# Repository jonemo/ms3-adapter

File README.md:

MS3 to Serial Port Adapter
==========================

What is this?
-------------

This repo contains a PCB design project including schematic, board layout, and component library.
The board is meant to provide an interface between three connectors:

* The DB15 connector (aka "VGA connector") attached to a Microscan MS3 barcode reader
* A DB9 connector plugged into the RS-232 "serial" port of a PC (or a USB-to-Serial converter or some other device with serial port)
* A 5.5mm center positive 5V DC power supply cable

When all three connectors are plugged in, the barcode reader is powered and can be communicated with from the PC.
For how to communicate with the barcode reader, please refer to Microscan's user manual or use [Microscan's ESP software](http://www.microscan.com/esp-easy-setup-program-software).
The Python library [microscan-driver](https://github.com/jonemo/microscan-driver) might be of use.

The files were created using Autodesk's Eagle 7.6.0.

Compatibility
-------------

I offer no guarantees that this PCB design works or
The board is almost certainly compatible with other Microscan barcode reader products, but it has only been tested with the MS3.

Sources
-------

The component library in this repo contains many footprints that are copied or modified from [Sparkfun's Eagle footprint library](https://github.com/sparkfun/SparkFun-Eagle-Libraries/).

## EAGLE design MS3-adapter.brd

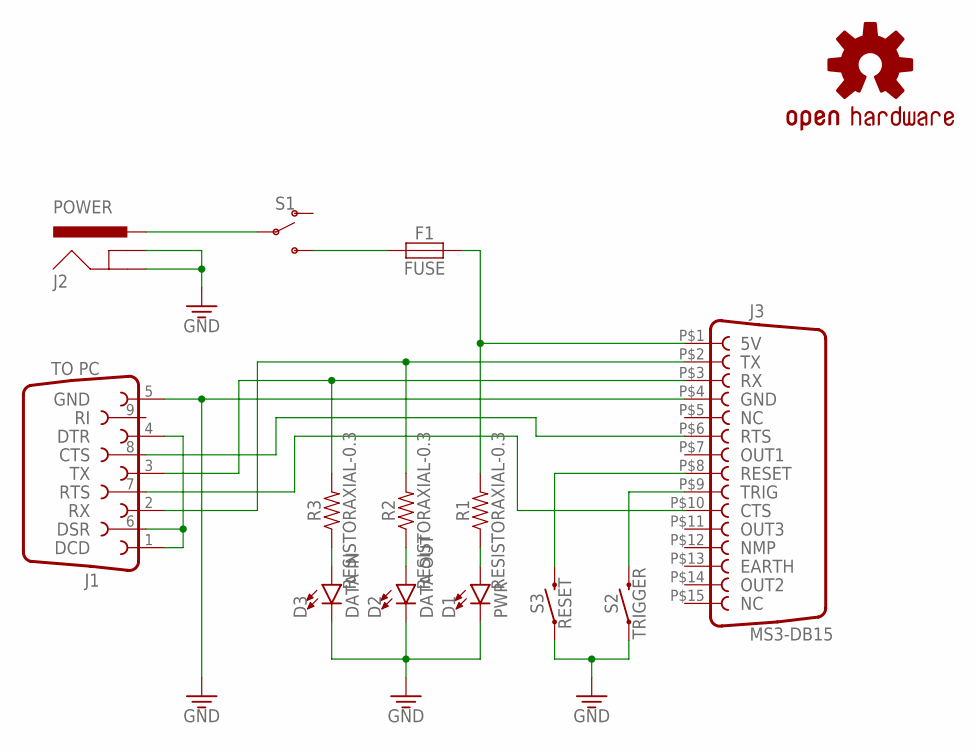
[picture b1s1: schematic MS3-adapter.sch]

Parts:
D1: PWR; LED_5MM
D2: DATA OUT; LED_5MM
D3: DATA IN; LED_5MM
F1: FUSE; FUSEHOLDER-PAIR-5MM
J1: TO PC; DB9-FEMALE
J2: POWER; POWER_JACK_PTH
J3: MS3-DB15; DB15-MALE
LOGO1: OSHW-LOGOS; OSHW-LOGO-S
R1, R2, R3: RESISTORAXIAL-0.3; AXIAL-0.3
S1: SWITCH-SPDT-PTH-11.6X4.0MM; SWITCH_SPDT_PTH_11.6X4.0MM
S2: TRIGGER; TACTILE_SWITCH_PTH_12MM
S3: RESET; TACTILE_SWITCH_PTH_12MM

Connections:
GND: D1.K (C), D2.K (C), D3.K (C), J1.5, J2.GND, J2.GNDBREAK, J3.P$4 (4), S2.1, S3.1
unnamed: J2.PWR, S1.2
unnamed: F1.P$1 (1), F1.P$2 (1), S1.3 (S)
unnamed: J1.3, J3.P$3 (3), R3.P$2 (2)
unnamed: J1.2, J3.P$2 (2), R2.P$2 (2)
unnamed: J1.1, J1.4, J1.6
unnamed: J1.7, J3.P$10 (10)
unnamed: J1.8, J3.P$6 (6)
unnamed: F1.P$3 (2), F1.P$4 (2), J3.P$1 (1), R1.P$2 (2)
unnamed: D2.A, R2.P$1 (1)
unnamed: D1.A, R1.P$1 (1)
unnamed: D3.A, R3.P$1 (1)
unnamed: J3.P$8 (8), S3.3 (2)
unnamed: J3.P$9 (9), S2.3 (2)

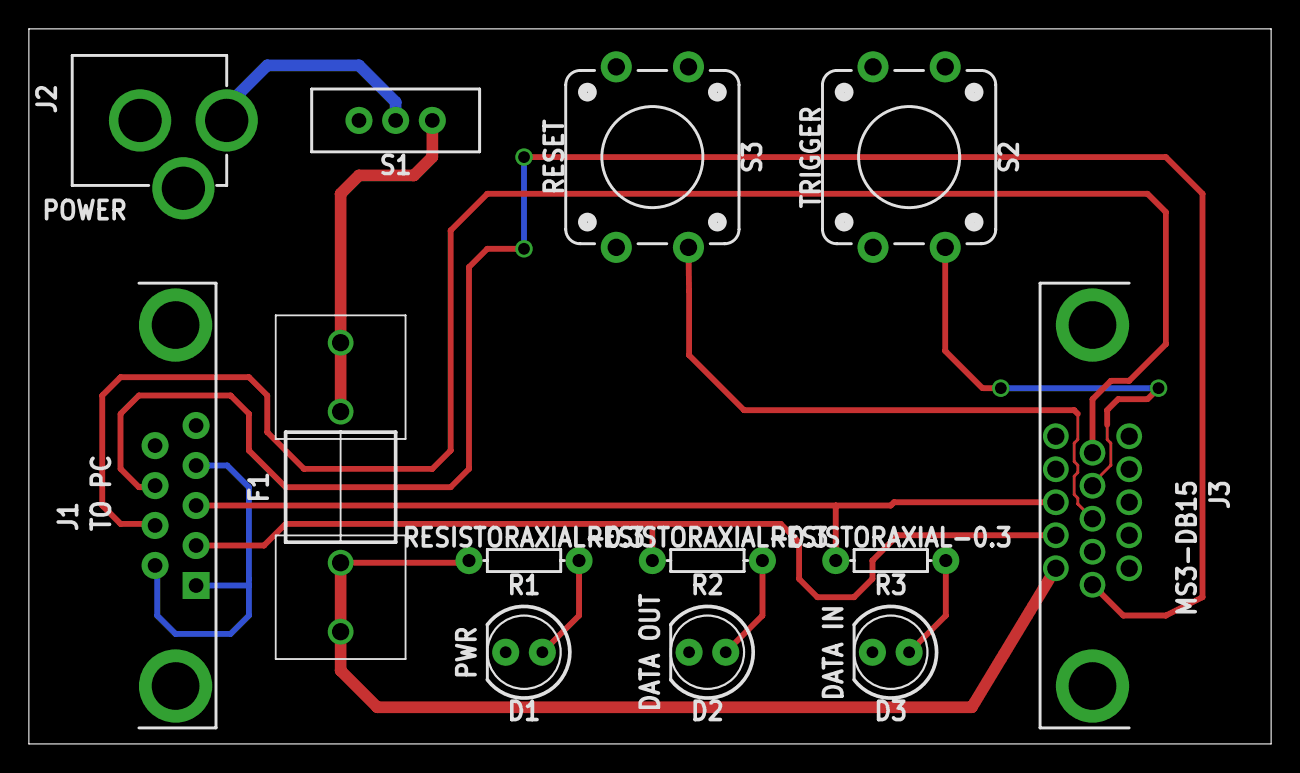
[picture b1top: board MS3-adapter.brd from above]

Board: 2 copper layers, 86.0 x 49.5 mm, 14 parts (1 on the bottom side), 14 nets.

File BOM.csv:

Part,Value,Device,Description,VENDOR,VENDOR_PN
D1,PWR,LED5MM (GREEN),LED (Generic),Sparkfun,COM-12903
D2,DATA OUT,LED5MM (BLUE),LED (Generic),Sparkfun,COM-12903
D3,DATA IN,LED5MM (YELLOW),LED (Generic),Sparkfun,COM-12903
F1,FUSE,FUSE,,Sparkfun,COM-10166
J1,TO PC,DB9-FEMALE,DB9 Connector,Sparkfun,PRT-00429
J2,POWER,POWER_JACK,Power Jack Connector,Sparkfun,PRT-00119
J3,TO MS3,DB15-MALE,,Digikey,A31927-ND
R1,,RESISTOR-AXIAL-0.3,Generic Resistor Package,Sparkfun,
R2,,RESISTOR-AXIAL-0.3,Generic Resistor Package,Sparkfun,
R3,,RESISTOR-AXIAL-0.3,Generic Resistor Package,Sparkfun,
S1,PWRSWITCH,SWITCH-SPDT-PTH-11.6X4.0MM,"Single Pole, Double Throw (SPDT) Switch",Sparkfun,COM-00102
S2,TRIGGER,MOMENTARY-SWITCH-SPST-PTH-12MM,Momentary Switch (Pushbutton) - SPST,Sparkfun,COM-09190
S3,RESET,MOMENTARY-SWITCH-SPST-PTH-12MM,Momentary Switch (Pushbutton) - SPST,Sparkfun,COM-09190
